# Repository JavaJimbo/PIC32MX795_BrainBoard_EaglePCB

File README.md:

# PIC32MX795_BrainBoard_EaglePCB
Eagle PCB layout files for my micro controller board using the PIC32MX795F512L

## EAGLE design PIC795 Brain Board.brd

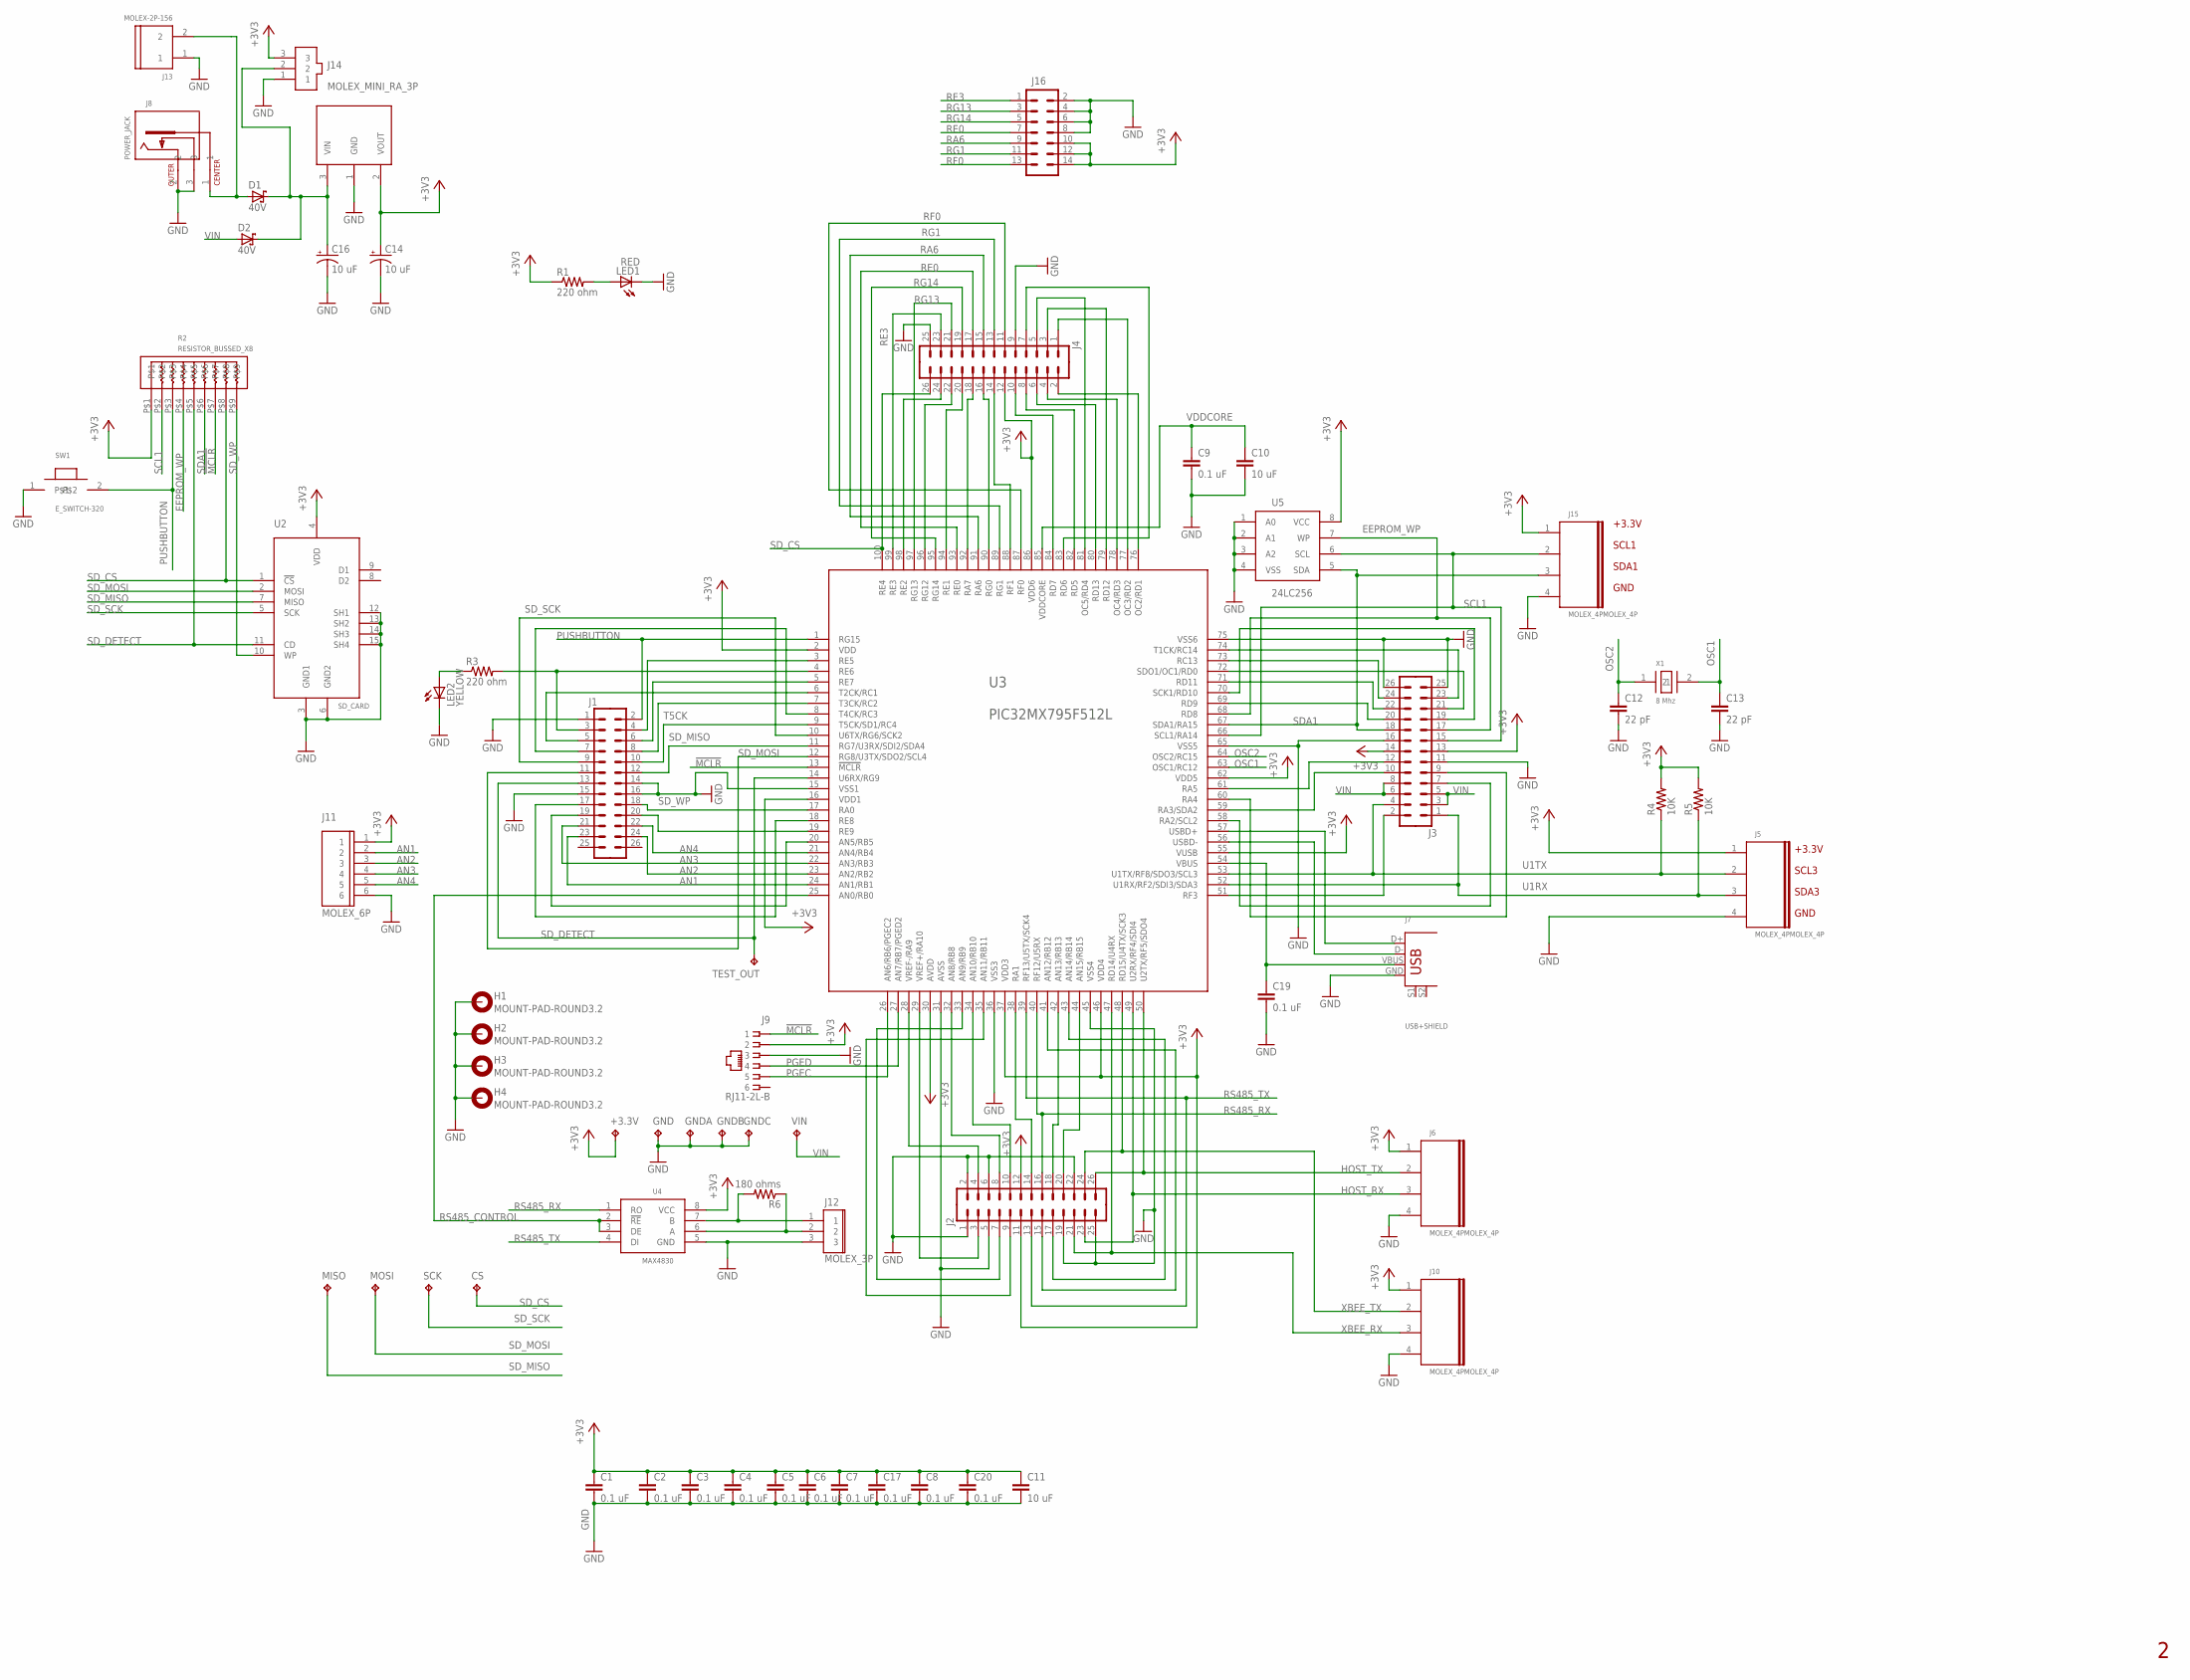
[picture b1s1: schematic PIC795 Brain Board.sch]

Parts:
+3.3V: TP; TESTPAD
C1, C2, C3, C4, C5, C6, C7, C8, C9, C17: 0.1 uF; 1206
C10, C11: 10 uF; 1206
C12, C13: 22 pF; C0805
C14, C16: 10 uF; E2,5-5
C19, C20: 0.1 uF; C5B2.5
CS: TP; TESTPAD
D1, D2: 40V; DO41-7.6
GND: TP; TESTPAD
GNDA: TP; TESTPAD
GNDB: TP; TESTPAD
GNDC: TP; TESTPAD
H1, H2, H3, H4: MOUNT-PAD-ROUND3.2; 3,2-PAD
J1, J2, J3, J4: M13X22X13; 2X13
J5, J6, J10, J15: MOLEX_4PMOLEX_4P; MOLEX_4P
J7: USB+SHIELD; USB-B-PTH
J8: POWER_JACK; POWER_JACK_PJ-202A
J9: RJ11-2L-B; RJ11-NO_SHIELD
J11: MOLEX_6P; MOLEX_6P_SLIM
J12: MOLEX_3P
J13: MOLEX-2P-156; MOLEX-156-2P
J14: MOLEX_MINI_RA_3P
J16: CONNECTOR_DUAL_ROW_14; 2X7
LED1: RED; LED5MM
LED2: YELLOW; LED5MM
MISO: TP; TESTPAD
MOSI: TP; TESTPAD
R1, R3: 220 ohm; 1/4_WATT
R2: RESISTOR_BUSSED_X8; RESISTOR_BUSSED
R4, R5: 10K; 1/4_WATT
R6: 180 ohms; 0204/7
SCK: TP; TESTPAD
SW1: E_SWITCH-320; E_SWITCH_320
TEST_OUT: TP; TESTPAD
U1: REGULATOR_LD1086_LDO; D2PAK
U2: SD_CARD; SD_CARD_TE_2041021
U3: PIC32MX795F512L; TQFP-100-14X14MM
U4: MAX4830; SOICN
U5: 24LC256; DIL08
VIN: TP; TESTPAD
X1: 8 Mhz; CRYSTAL-SMD

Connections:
!MCLR: J9.1, R2.P$7, U3.13 (!MCLR)
+3V3: +3.3V.P$1, C1.A (1), C2.A (1), C3.A (1), C4.A (1), C5.A (1), C6.A (1), C7.A (1), C8.A (1), C11.A (1), C14.+, C17.A (1), C20.1, J2.11, J2.12, J3.13, J3.14, J4.12, J5.1, J6.1, J9.2, J10.1, J11.1, J14.3, J15.1, J16.10, J16.12, J16.14, R1.1, R2.P$1, R4.2, R5.2, U1.2 (VOUT), U2.4 (VDD), U3.2 (VDD), U3.16 (VDD1), U3.30 (AVDD), U3.37 (VDD3), U3.46 (VDD4), U3.55 (VUSB), U3.62 (VDD5), U3.86 (VDD6), U4.8 (VCC), U5.8 (VCC)
AN1: J1.23, J11.2, U3.24 (AN1/RB1)
AN2: J1.24, J11.3, U3.23 (AN2/RB2)
AN3: J1.21, J11.4, U3.22 (AN3/RB3)
AN4: J1.22, J11.5, U3.21 (AN4/RB4)
EEPROM_WP: J3.17, R2.P$4, U3.68 (RD8), U5.7 (WP)
GND: C1.C (2), C2.C (2), C3.C (2), C4.C (2), C5.C (2), C6.C (2), C7.C (2), C8.C (2), C9.C (2), C10.C (2), C11.C (2), C12.2, C13.2, C14.-, C16.-, C17.C (2), C19.2, C20.2, GND.P$1, GNDA.P$1, GNDB.P$1, GNDC.P$1, H1.B3,2, H2.B3,2, H3.B3,2, H4.B3,2, J1.1, J1.14, J1.15, J1.16, J2.1, J2.2, J2.5, J2.6, J2.19, J2.22, J2.25, J3.11, J3.16, J3.25, J3.26, J4.9, J4.25, J5.4, J6.4, J7.GND, J8.2, J8.3, J9.3, J10.4, J11.6, J12.3, J13.1, J14.1, J15.4, J16.2, J16.4, J16.6, J16.8, LED1.K (C), LED2.K (C), SW1.1, U1.1 (GND), U2.3 (GND1), U2.6 (GND2), U2.12 (SH1), U2.13 (SH2), U2.14 (SH3), U2.15 (SH4), U3.15 (VSS1), U3.31 (AVSS), U3.36 (VSS3), U3.45 (VSS4), U3.65 (VSS5), U3.75 (VSS6), U4.5 (GND), U5.1 (A0), U5.2 (A1), U5.3 (A2), U5.4 (VSS)
HOST_RX: J2.23, J6.3, U3.49 (U2RX/RF4/SDI4)
HOST_TX: J2.26, J6.2, U3.50 (U2TX/RF5/SDO4)
unnamed: J3.2, U3.51 (RF3)
unnamed: LED2.A, R3.1
unnamed: J2.8, U3.32 (AN8/RB8)
unnamed: J7.D+, U3.57 (USBD+)
unnamed: J3.10, U3.59 (RA3/SDA2)
unnamed: J3.12, U3.61 (RA5)
unnamed: D1.A, J8.1, J13.2
unnamed: C16.+, D1.C, D2.C, J14.2, U1.3 (VIN)
unnamed: J3.20, U3.69 (RD9)
unnamed: J3.22, U3.71 (RD11)
unnamed: J3.24, U3.73 (RC13)
unnamed: C19.1, J7.VBUS, U3.54 (VBUS)
unnamed: J7.D-, U3.56 (USBD-)
unnamed: J3.7, U3.58 (RA2/SCL2)
unnamed: J3.9, U3.60 (RA4)
unnamed: J3.23, U3.74 (T1CK/RC14)
unnamed: J3.21, U3.72 (SDO1/OC1/RD0)
unnamed: J3.19, U3.70 (SCK1/RD10)
unnamed: LED1.A, R1.2
unnamed: J12.1, R6.2, U4.7 (B)
unnamed: J2.4, U3.28 (VREF-/RA9)
unnamed: J12.2, R6.1, U4.6 (A)
unnamed: J2.10, U3.34 (AN10/RB10)
unnamed: J2.14, U3.38 (RA1)
unnamed: J2.18, U3.42 (AN13/RB13)
unnamed: J2.20, U3.44 (AN15/RB15)
unnamed: J2.3, U3.29 (VREF+/RA10)
unnamed: J2.7, U3.33 (AN9/RB9)
unnamed: J2.9, U3.35 (AN11/RB11)
unnamed: J2.17, U3.43 (AN14/RB14)
unnamed: J2.15, U3.41 (AN12/RB12)
unnamed: J4.2, U3.76 (OC2/RD1)
unnamed: J4.4, U3.78 (OC4/RD3)
unnamed: J4.6, U3.80 (RD13)
unnamed: J4.8, U3.82 (RD5)
unnamed: J4.10, U3.84 (RD7)
unnamed: J4.14, U3.88 (RF1)
unnamed: J4.16, U3.90 (RG0)
unnamed: J4.18, U3.92 (RA7)
unnamed: J4.20, U3.94 (RE1)
unnamed: J4.22, U3.96 (RG12)
unnamed: J4.24, U3.98 (RE2)
unnamed: J4.1, U3.77 (OC3/RD2)
unnamed: J4.3, U3.79 (RD12)
unnamed: J4.5, U3.81 (OC5/RD4)
unnamed: J4.7, U3.83 (RD6)
unnamed: J1.4, U3.3 (RE5)
unnamed: J1.6, U3.5 (RE7)
unnamed: J1.8, U3.7 (T3CK/RC2)
unnamed: J1.20, U3.19 (RE9)
unnamed: J1.3, R3.2, U3.4 (RE6)
unnamed: J1.5, U3.6 (T2CK/RC1)
unnamed: J1.7, U3.8 (T4CK/RC3)
unnamed: J1.19, U3.20 (AN5/RB5)
unnamed: J1.17, U3.18 (RE8)
OSC1: C13.1, U3.63 (OSC1/RC12), X1.2
OSC2: C12.1, U3.64 (OSC2/RC15), X1.1
PGEC: J9.5, U3.26 (AN6/RB6/PGEC2)
PGED: J9.4, U3.27 (AN7/RB7/PGED2)
PUSHBUTTON: J1.2, R2.P$3, SW1.2, U3.1 (RG15)
RA6: J4.15, J16.9, U3.91 (RA6)
RE0: J4.17, J16.7, U3.93 (RE0)
RE3: J4.23, J16.1, U3.99 (RE3)
RF0: J4.11, J16.13, U3.87 (RF0)
RG1: J4.13, J16.11, U3.89 (RG1)
RG13: J4.21, J16.3, U3.97 (RG13)
RG14: J4.19, J16.5, U3.95 (RG14)
RS485_CONTROL: U3.25 (AN0/RB0), U4.2 (!RE), U4.3 (DE)
RS485_RX: J2.16, U3.40 (RF12/U5RX), U4.1 (RO)
RS485_TX: J2.13, U3.39 (RF13/U5TX/SCK4), U4.4 (DI)
SCL1: J3.15, J15.2, R2.P$2, U3.66 (SCL1/RA14), U5.6 (SCL)
SDA1: J3.18, J15.3, R2.P$6, U3.67 (SDA1/RA15), U5.5 (SDA)
SD_CS: CS.P$1, J4.26, R2.P$8, U2.1 (!CS), U3.100 (RE4)
SD_DETECT: J1.13, R2.P$5, TEST_OUT.P$1, U2.11 (CD), U3.14 (U6RX/RG9)
SD_MISO: J1.12, MISO.P$1, U2.7 (MISO), U3.11 (RG7/U3RX/SDI2/SDA4)
SD_MOSI: J1.11, MOSI.P$1, U2.2 (MOSI), U3.12 (RG8/U3TX/SDO2/SCL4)
SD_SCK: J1.9, SCK.P$1, U2.5 (SCK), U3.10 (U6TX/RG6/SCK2)
SD_WP: J1.18, R2.P$9, U2.10 (WP), U3.17 (RA0)
T5CK: J1.10, U3.9 (T5CK/SD1/RC4)
U1RX: J3.1, J5.3, R5.1, U3.52 (U1RX/RF2/SDI3/SDA3)
U1TX: J3.4, J5.2, R4.1, U3.53 (U1TX/RF8/SDO3/SCL3)
VDDCORE: C9.A (1), C10.A (1), U3.85 (VDDCORE)
VIN: D2.A, J3.3, J3.5, J3.6, J3.8, VIN.P$1
XBEE_RX: J2.21, J10.3, U3.47 (RD14/U4RX)
XBEE_TX: J2.24, J10.2, U3.48 (RD15/U4TX/SCK3)

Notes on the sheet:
SCL3
SDA3
GND
+3.3V
SCL1
SDA1

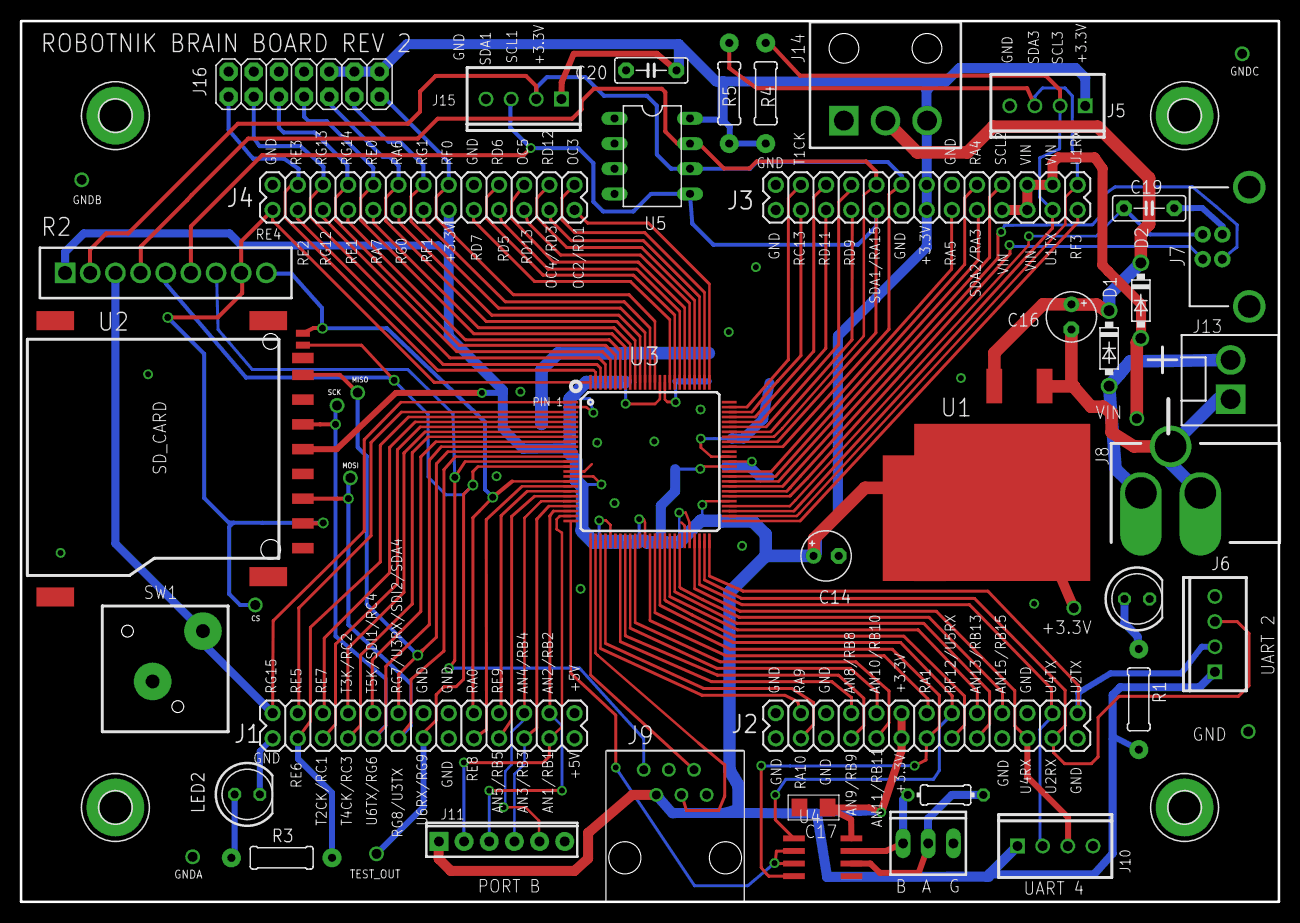
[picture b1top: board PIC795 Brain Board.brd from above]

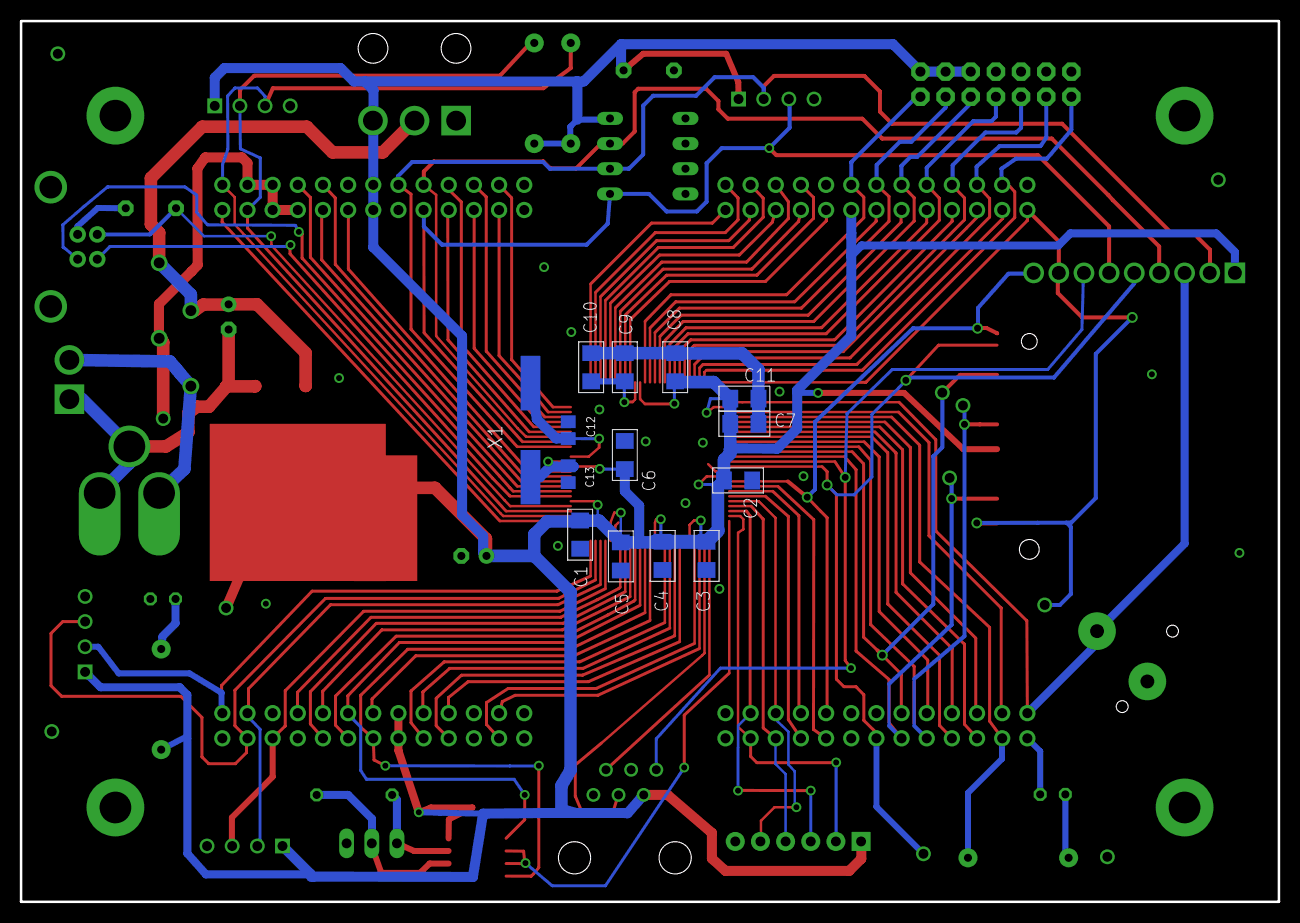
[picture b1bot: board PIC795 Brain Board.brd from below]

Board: 2 copper layers, 127.0 x 88.9 mm, 66 parts (14 on the bottom side), 95 nets.

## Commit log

2019-07-10 Add files via upload
    First version, untested with four dual row headers, based on SnadPIC and UBW32 boards
2019-07-11 Add files via upload
    Added BOM with DigiKey part numbers for first build 7/11/19
2019-07-21 Add files via upload
    Minor changes for Rev 2
2019-08-12 Add files via upload
    Includes latest changes for Rev 2. Shipped to PCB fab 8-12-19

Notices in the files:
parts and their libraries:
SparkFun-Connectors: Licensing: Creative Commons ShareAlike 4.0 International - https://creativecommons.org/licenses/by-sa/4.0
